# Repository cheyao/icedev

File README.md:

# Icedev

A ICE40 FPGA breakout board. With built in clock, voltage regs, ram and rom.

- 64 KiB of onboard flash
- 128 MiB of NOR flash
- 16 MHZ onboard Crystal
- 256 KiB of built-in RAM

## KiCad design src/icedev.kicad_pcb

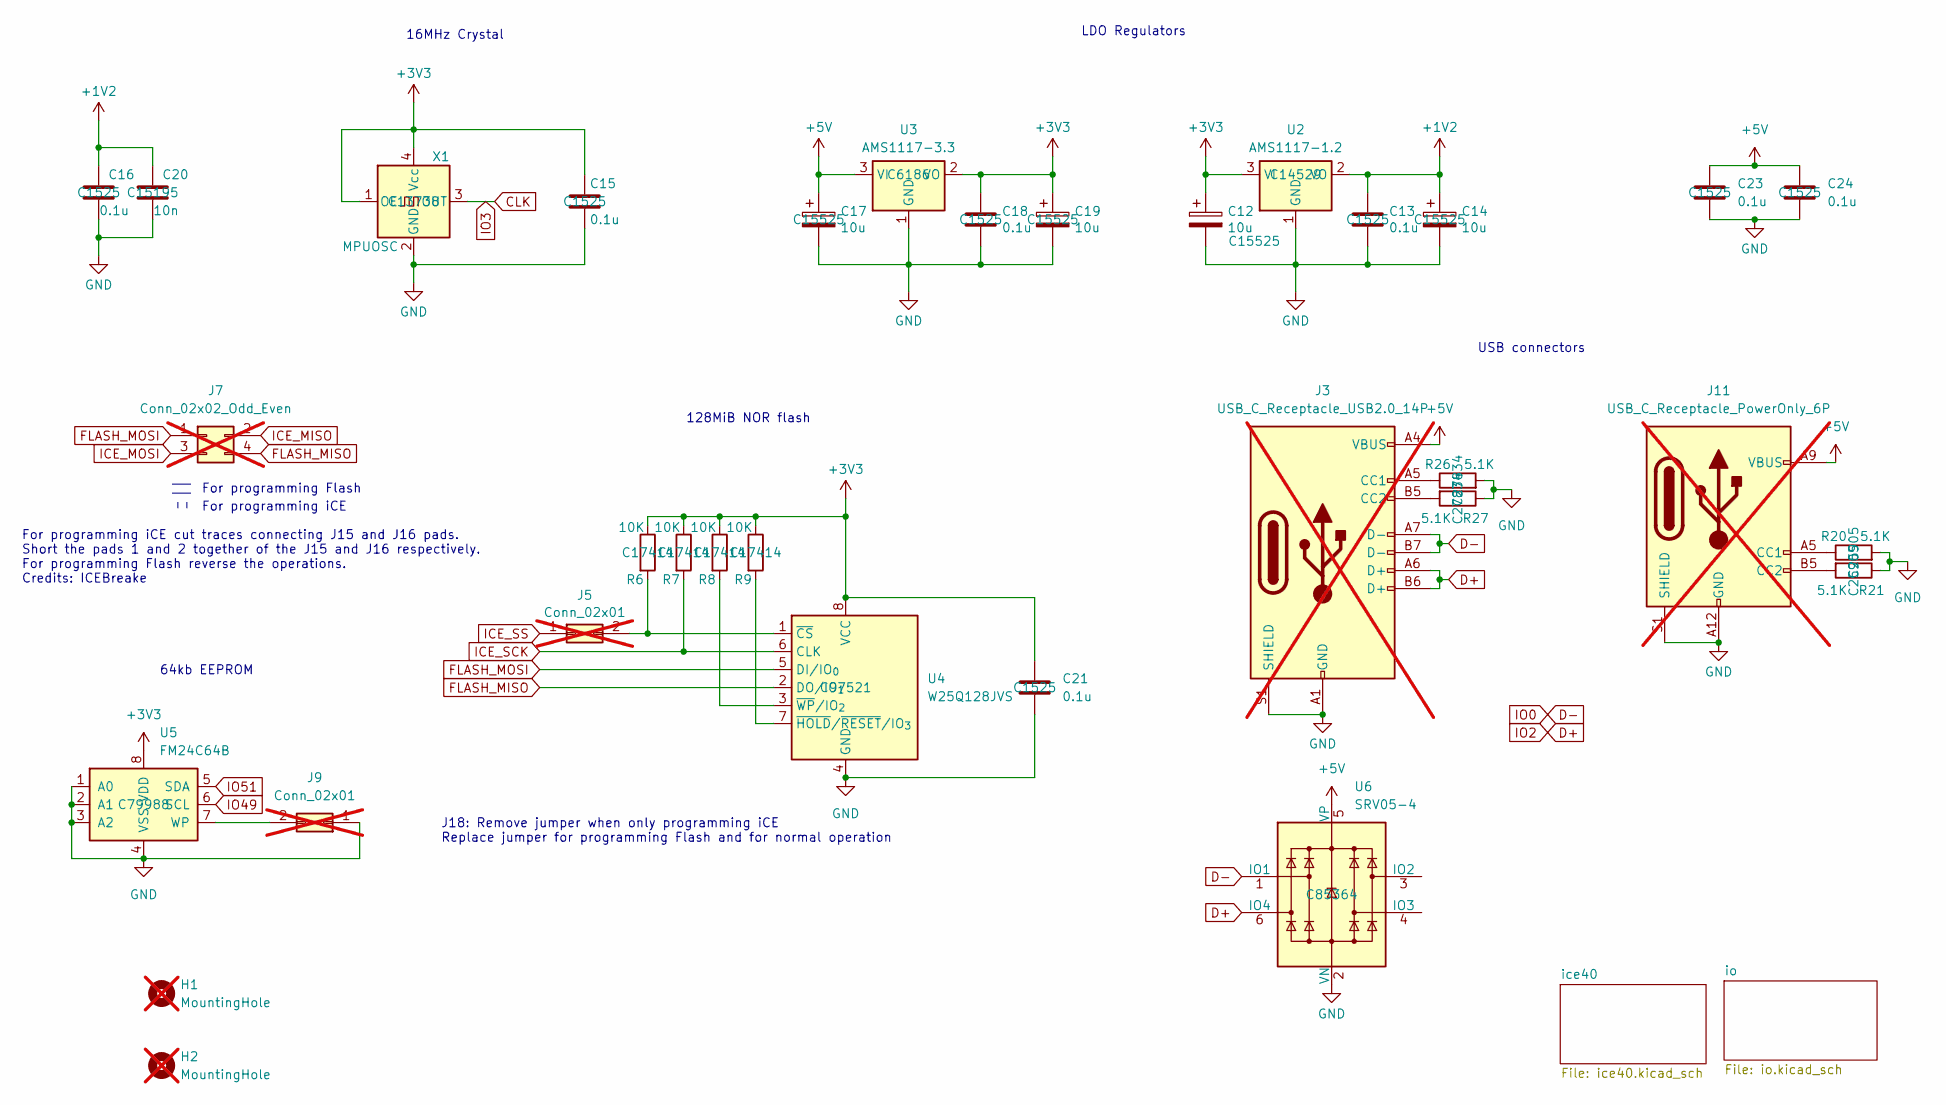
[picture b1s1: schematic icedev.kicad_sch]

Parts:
C12, C14, C17, C19: 10u; C_0402_1005Metric; JLCPCB Part # C15525
C13, C15, C16, C18, C21, C23, C24: 0.1u; C_0402_1005Metric; JLCPCB Part # C1525
C20: 10n; C_0402_1005Metric; JLCPCB Part # C15195
H1, H2: MountingHole; MountingHole_2.2mm_M2; not fitted
J3: USB_C_Receptacle_USB2.0_14P; USB_C_Receptacle_GCT_USB4105-xx-A_16P_TopMnt_Horizontal; not fitted
J5, J9: Conn_02x01; PinHeader_2x01_P2.54mm_Vertical; not fitted
J7: Conn_02x02_Odd_Even; PinSocket_2x02_P2.54mm_Vertical; not fitted
J11: USB_C_Receptacle_PowerOnly_6P; USB_C_Receptacle_GCT_USB4135-GF-A_6P_TopMnt_Horizontal; not fitted
R6, R7, R8, R9: 10K; R_0805_2012Metric; JLCPCB Part # C17414
R20, R21: 5.1K; R_0402_1005Metric; JLCPCB Part # C25905
R26, R27: 5.1K; R_0805_2012Metric; JLCPCB Part # C27834
U2: AMS1117-1.2; SOT-223-3_TabPin2; JLCPCB Part # C14529
U3: AMS1117-3.3; SOT-223-3_TabPin2; JLCPCB Part # C6186
U4: W25Q128JVS; SOIC-8_5.3x5.3mm_P1.27mm; JLCPCB Part # C97521
U5: FM24C64B; SOIC-8_3.9x4.9mm_P1.27mm; JLCPCB Part # C79988
U6: SRV05-4; SOT-23-6-routable; JLCPCB Part # C85364
X1: MPUOSC; Oscillator_SMD_Abracon_ASE-4Pin_3.2x2.5mm; JLCPCB Part # C13738

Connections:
+1V2: C13.1, C14.1, C16.1, C20.1, U2.2 (VO); also elsewhere on the board
+3V3: C12.1, C15.1, C18.1, C19.1, C21.1, R6.1, R7.1, R8.1, R9.1, U2.3 (VI), U3.2 (VO), U4.8 (VCC), U5.8 (VDD), X1.1 (OE), X1.4 (Vcc); also elsewhere on the board
+5V: C17.1, C23.1, C24.1, J3.A4 (VBUS), J3.A9 (VBUS), J3.B4 (VBUS), J3.B9 (VBUS), J11.A9 (VBUS), J11.B9 (VBUS), U3.3 (VI), U6.5 (VP); also elsewhere on the board
CLK: X1.3 (OUT); also elsewhere on the board
D+: J3.A6 (D+), J3.B6 (D+), U6.6 (IO4); also elsewhere on the board
D-: J3.A7 (D-), J3.B7 (D-), U6.1 (IO1); also elsewhere on the board
FLASH_MISO: J7.4, U4.2 (DO/IO_{1}); also elsewhere on the board
FLASH_MOSI: J7.1, U4.5 (DI/IO_{0}); also elsewhere on the board
GND: C12.2, C13.2, C14.2, C15.2, C16.2, C17.2, C18.2, C19.2, C20.2, C21.2, C23.2, C24.2, J3.A1 (GND), J3.A12 (GND), J3.B1 (GND), J3.B12 (GND), J3.S1 (SHIELD), J9.1, J11.A12 (GND), J11.B12 (GND), J11.S1 (SHIELD), R20.2, R21.1, R26.2, R27.1, U2.1 (GND), U3.1 (GND), U4.4 (GND), U5.1 (A0), U5.2 (A1), U5.3 (A2), U5.4 (VSS), U6.2 (VN), X1.2 (GND); also elsewhere on the board
ICE_MISO: J7.2; also elsewhere on the board
ICE_MOSI: J7.3; also elsewhere on the board
ICE_SCK: R7.2, U4.6 (CLK); also elsewhere on the board
ICE_SS: J5.1; also elsewhere on the board
IO49: U5.6 (SCL); also elsewhere on the board
IO51: U5.5 (SDA); also elsewhere on the board
unnamed: J3.A5 (CC1), R26.1
unnamed 52: J3.B5 (CC2), R27.2; also elsewhere on the board
unnamed: J5.2, R6.2, U4.1 (~CS)
unnamed: J9.2, U5.7 (WP)
unnamed: J11.A5 (CC1), R20.1
unnamed: J11.B5 (CC2), R21.2
unnamed: R9.2, U4.7 (~HOLD/~RESET/IO_{3})
unnamed: R8.2, U4.3 (~WP/IO_{2})

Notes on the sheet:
For programming Flash
J18: Remove jumper when only programming iCE Replace jumper for programming Flash and for normal operation
64kb EEPROM
16MHz Crystal
USB connectors
For programming iCE cut traces connecting J15 and J16 pads. Short the pads 1 and 2 together of the J15 and J16 respectively. For programming Flash reverse the operations. Credits: ICEBreake
128MiB NOR flash
LDO Regulators
For programming iCE

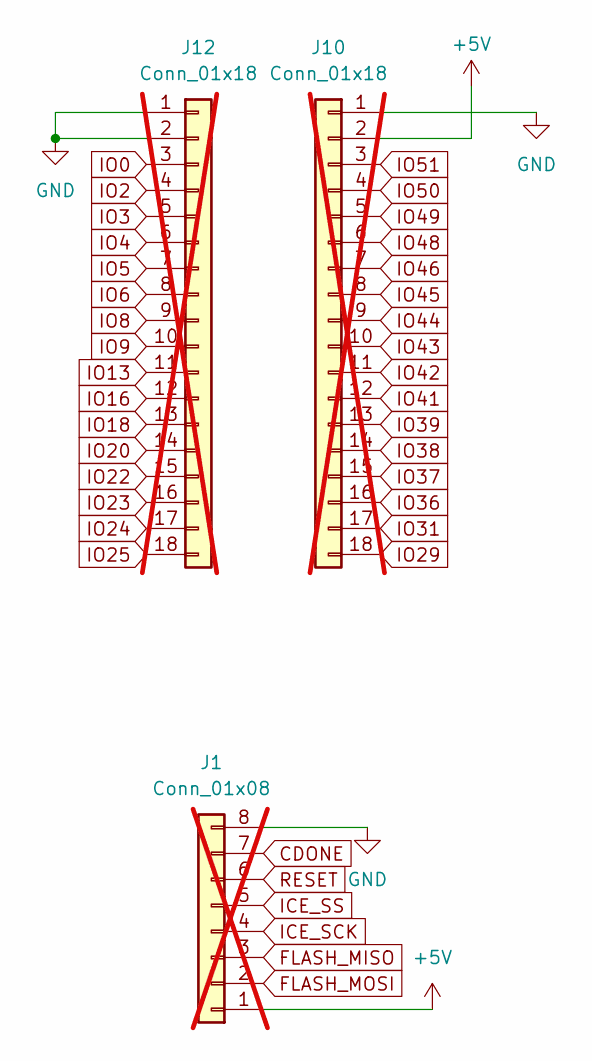
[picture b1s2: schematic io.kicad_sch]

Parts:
J1: Conn_01x08; PinSocket_1x08_P2.54mm_Vertical; not fitted
J10, J12: Conn_01x18; PinSocket_1x18_P2.54mm_Vertical; not fitted

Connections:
+5V: J1.1, J10.2; also elsewhere on the board
CDONE: J1.7; also elsewhere on the board
FLASH_MISO: J1.3; also elsewhere on the board
FLASH_MOSI: J1.2; also elsewhere on the board
GND: J1.8, J10.1, J12.1, J12.2; also elsewhere on the board
ICE_SCK: J1.4; also elsewhere on the board
ICE_SS: J1.5; also elsewhere on the board
RESET: J1.6; also elsewhere on the board

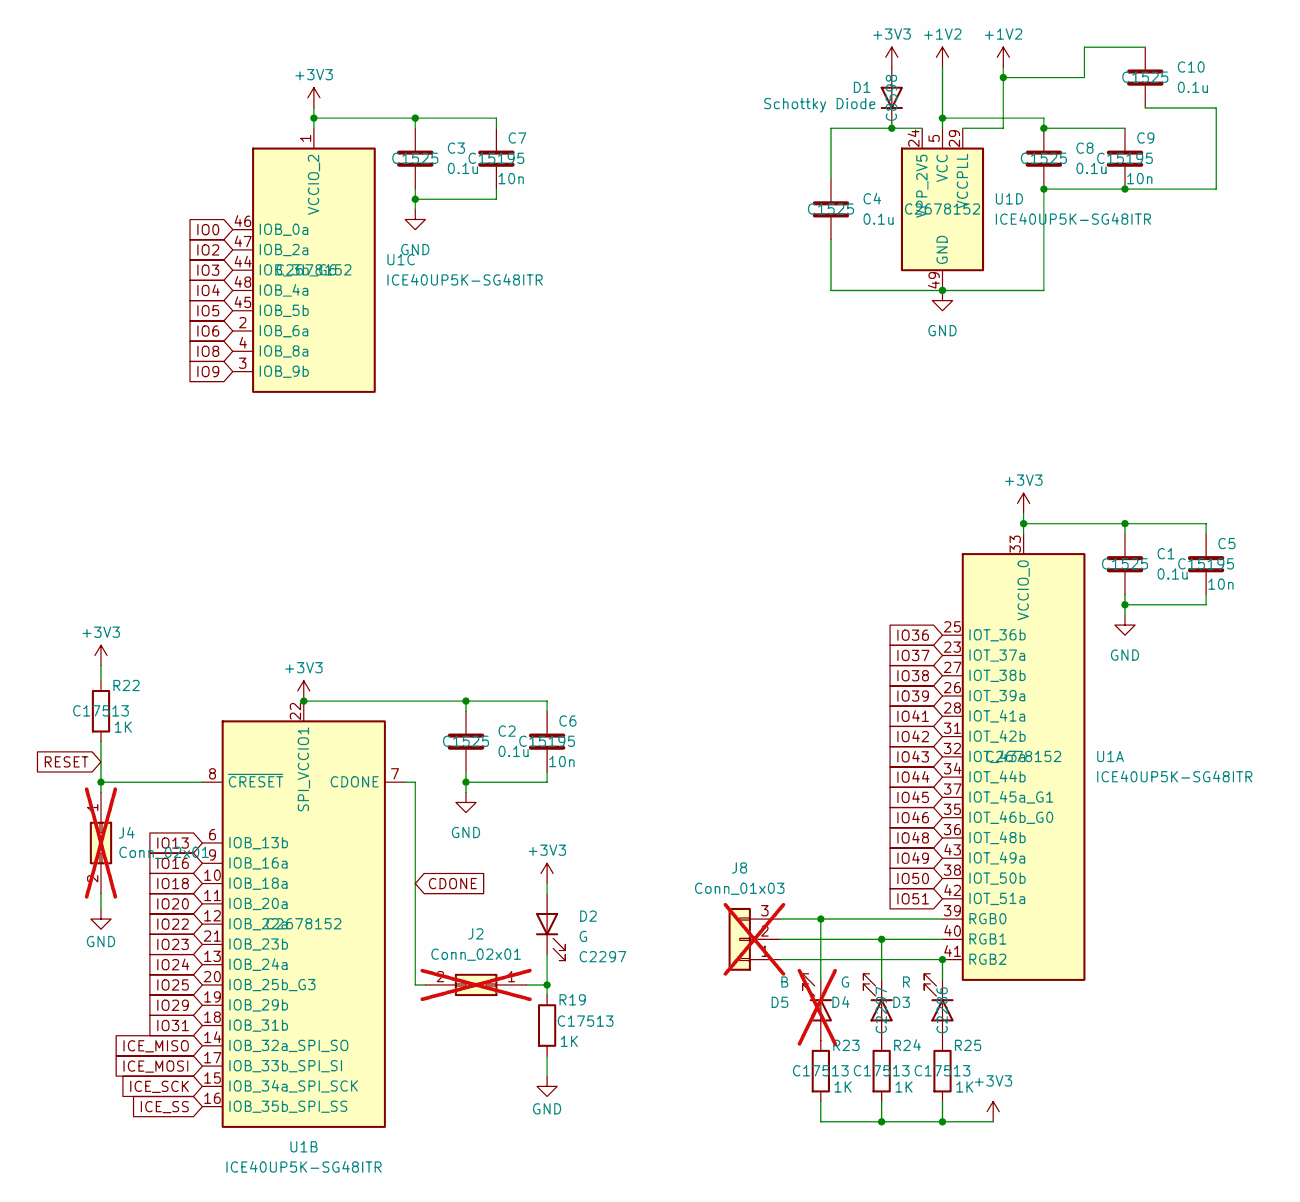
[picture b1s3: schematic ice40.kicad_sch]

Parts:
C1, C2, C3, C4, C8, C10: 0.1u; C_0402_1005Metric; JLCPCB Part # C1525
C5, C6, C7, C9: 10n; C_0402_1005Metric; JLCPCB Part # C15195
D1: Schottky Diode; D_SOD-123; JLCPCB Part # C8598
D2, D4: G; LED_0805_2012Metric; JLCPCB Part # C2297
D3: R; LED_0603_1608Metric; JLCPCB Part # C2286
D5: B; LED_0201_0603Metric_Pad0.64x0.40mm_HandSolder; not fitted
J2, J4: Conn_02x01; PinHeader_2x01_P2.54mm_Vertical; not fitted
J8: Conn_01x03; PinHeader_1x03_P2.54mm_Vertical; not fitted
R19, R22, R23, R24, R25: 1K; R_0805_2012Metric; JLCPCB Part # C17513
U1: ICE40UP5K-SG48ITR; QFN-48-1EP_7x7mm_P0.5mm_EP5.6x5.6mm; JLCPCB Part # C2678152

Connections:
+1V2: C8.1, C9.1, C10.1, U1.5 (VCC), U1.29 (VCCPLL), U1.30 (VCC); also elsewhere on the board
+3V3: C1.1, C2.1, C3.1, C5.1, C6.1, C7.1, D1.2 (A), D2.2 (A), R22.1, R23.2, R24.2, R25.2, U1.1 (VCCIO_2), U1.22 (SPI_VCCIO1), U1.33 (VCCIO_0); also elsewhere on the board
CDONE: J2.2, U1.7 (CDONE); also elsewhere on the board
CLK: U1.44 (IOB_3b_G6); also elsewhere on the board
D+: U1.47 (IOB_2a); also elsewhere on the board
D-: U1.46 (IOB_0a); also elsewhere on the board
GND: C1.2, C2.2, C3.2, C4.2, C5.2, C6.2, C7.2, C8.2, C9.2, C10.2, J4.2, R19.2, U1.49 (GND); also elsewhere on the board
ICE_MISO: U1.14 (IOB_32a_SPI_SO); also elsewhere on the board
ICE_MOSI: U1.17 (IOB_33b_SPI_SI); also elsewhere on the board
ICE_SCK: U1.15 (IOB_34a_SPI_SCK); also elsewhere on the board
ICE_SS: U1.16 (IOB_35b_SPI_SS); also elsewhere on the board
IO4: U1.48 (IOB_4a); also elsewhere on the board
IO5: U1.45 (IOB_5b); also elsewhere on the board
IO6: U1.2 (IOB_6a); also elsewhere on the board
IO8: U1.4 (IOB_8a); also elsewhere on the board
IO9: U1.3 (IOB_9b); also elsewhere on the board
IO13: U1.6 (IOB_13b); also elsewhere on the board
IO16: U1.9 (IOB_16a); also elsewhere on the board
IO18: U1.10 (IOB_18a); also elsewhere on the board
IO20: U1.11 (IOB_20a); also elsewhere on the board
IO22: U1.12 (IOB_22a); also elsewhere on the board
IO23: U1.21 (IOB_23b); also elsewhere on the board
IO24: U1.13 (IOB_24a); also elsewhere on the board
IO25: U1.20 (IOB_25b_G3); also elsewhere on the board
IO29: U1.19 (IOB_29b); also elsewhere on the board
IO31: U1.18 (IOB_31b); also elsewhere on the board
IO36: U1.25 (IOT_36b); also elsewhere on the board
IO37: U1.23 (IOT_37a); also elsewhere on the board
IO38: U1.27 (IOT_38b); also elsewhere on the board
IO39: U1.26 (IOT_39a); also elsewhere on the board
IO41: U1.28 (IOT_41a); also elsewhere on the board
IO42: U1.31 (IOT_42b); also elsewhere on the board
IO43: U1.32 (IOT_43a); also elsewhere on the board
IO44: U1.34 (IOT_44b); also elsewhere on the board
IO45: U1.37 (IOT_45a_G1); also elsewhere on the board
IO46: U1.35 (IOT_46b_G0); also elsewhere on the board
IO48: U1.36 (IOT_48b); also elsewhere on the board
IO49: U1.43 (IOT_49a); also elsewhere on the board
IO50: U1.38 (IOT_50b); also elsewhere on the board
IO51: U1.42 (IOT_51a); also elsewhere on the board
unnamed: C4.1, D1.1 (K), U1.24 (VPP_2V5)
unnamed: D2.1 (K), J2.1, R19.1
unnamed: D3.2 (A), R25.1
unnamed: D3.1 (K), J8.1, U1.41 (RGB2)
unnamed: D4.2 (A), R24.1
unnamed: D4.1 (K), J8.2, U1.40 (RGB1)
unnamed: D5.2 (A), R23.1
unnamed: D5.1 (K), J8.3, U1.39 (RGB0)
RESET: J4.1, R22.2, U1.8 (~CRESET); also elsewhere on the board

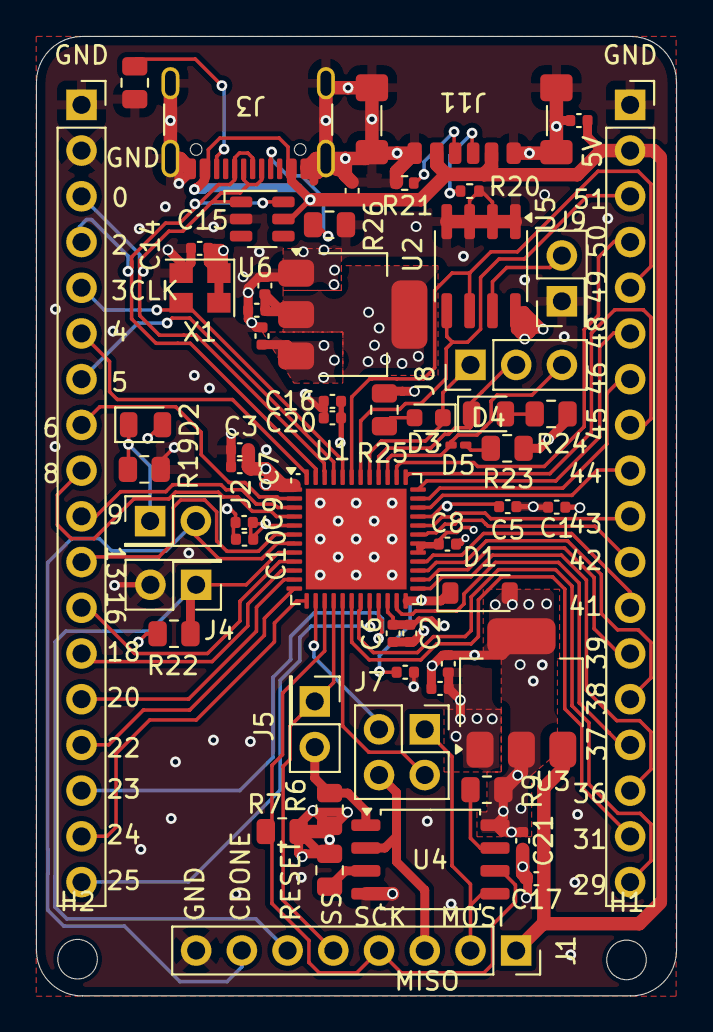
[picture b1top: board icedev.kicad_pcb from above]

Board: 4 copper layers, 35.6 x 53.3 mm, 60 parts (0 on the bottom side), 60 nets.

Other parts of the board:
5V: 0.1u; C_0402_1005Metric
GND: Conn_01x18; PinSocket_1x18_P2.54mm_Vertical
GND#2: 5.1K; R_0805_2012Metric
GND#3: Conn_01x18; PinSocket_1x18_P2.54mm_Vertical

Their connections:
+5V: 5V.1, GND#3.2; also elsewhere on the board
CLK: GND.5; also elsewhere on the board
D+: GND.4; also elsewhere on the board
D-: GND.3; also elsewhere on the board
GND: 5V.2, GND.1, GND.2, GND#2.1, GND#3.1; also elsewhere on the board
IO4: GND.6; also elsewhere on the board
IO5: GND.7; also elsewhere on the board
IO6: GND.8; also elsewhere on the board
IO8: GND.9; also elsewhere on the board
IO9: GND.10; also elsewhere on the board
IO13: GND.11; also elsewhere on the board
IO16: GND.12; also elsewhere on the board
IO18: GND.13; also elsewhere on the board
IO20: GND.14; also elsewhere on the board
IO22: GND.15; also elsewhere on the board
IO23: GND.16; also elsewhere on the board
IO24: GND.17; also elsewhere on the board
IO25: GND.18; also elsewhere on the board
IO29: GND#3.18; also elsewhere on the board
IO31: GND#3.17; also elsewhere on the board
IO36: GND#3.16; also elsewhere on the board
IO37: GND#3.15; also elsewhere on the board
IO38: GND#3.14; also elsewhere on the board
IO39: GND#3.13; also elsewhere on the board
IO41: GND#3.12; also elsewhere on the board
IO42: GND#3.11; also elsewhere on the board
IO43: GND#3.10; also elsewhere on the board
IO44: GND#3.9; also elsewhere on the board
IO45: GND#3.8; also elsewhere on the board
IO46: GND#3.7; also elsewhere on the board
IO48: GND#3.6; also elsewhere on the board
IO49: GND#3.5; also elsewhere on the board
IO50: GND#3.4; also elsewhere on the board
IO51: GND#3.3; also elsewhere on the board
unnamed 52: GND#2.2; also elsewhere on the board

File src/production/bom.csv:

Designator,Footprint,Quantity,Value,LCSC Part #
"5V, C1, C10, C13, C15, C16, C18, C2, C21, C23, C3, C4, C8",0402,13,0.1u,C1525
"C12, C14, C17, C19",0402,4,10u,C15525
"C20, C5, C6, C7, C9",0402,5,10n,C15195
D1,D_SOD-123,1,Schottky Diode,C8598
"D2, D4",0805,2,G,C2297
D3,0603,1,R,C2286
"GND_3, R26",0805,2,5.1K,C27834
"R19, R22, R23, R24, R25",0805,5,1K,C17513
"R20, R21",0402,2,5.1K,C25905
"R6, R7, R8, R9",0805,4,10K,C17414
U1,QFN-48-1EP_7x7mm_P0.5mm_EP5.6x5.6mm,1,ICE40UP5K-SG48ITR,C2678152
U2,SOT-223-3_TabPin2,1,AMS1117-1.2,C14529
U3,SOT-223-3_TabPin2,1,AMS1117-3.3,C6186
U4,SOIC-8_5.3x5.3mm_P1.27mm,1,W25Q128JVS,C97521
U5,SOIC-8_3.9x4.9mm_P1.27mm,1,FM24C64B,C79988
U6,SOT-23-6-routable,1,SRV05-4,C85364
X1,Oscillator_SMD_Abracon_ASE-4Pin_3.2x2.5mm,1,MPUOSC,C13738

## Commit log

2025-04-15 Init
2025-04-15 Add LICENSE
2025-04-16 Rev 2
2025-04-16 Some more improvements and readme images
2025-04-16 Off to prod!
2025-04-21 Add specs
